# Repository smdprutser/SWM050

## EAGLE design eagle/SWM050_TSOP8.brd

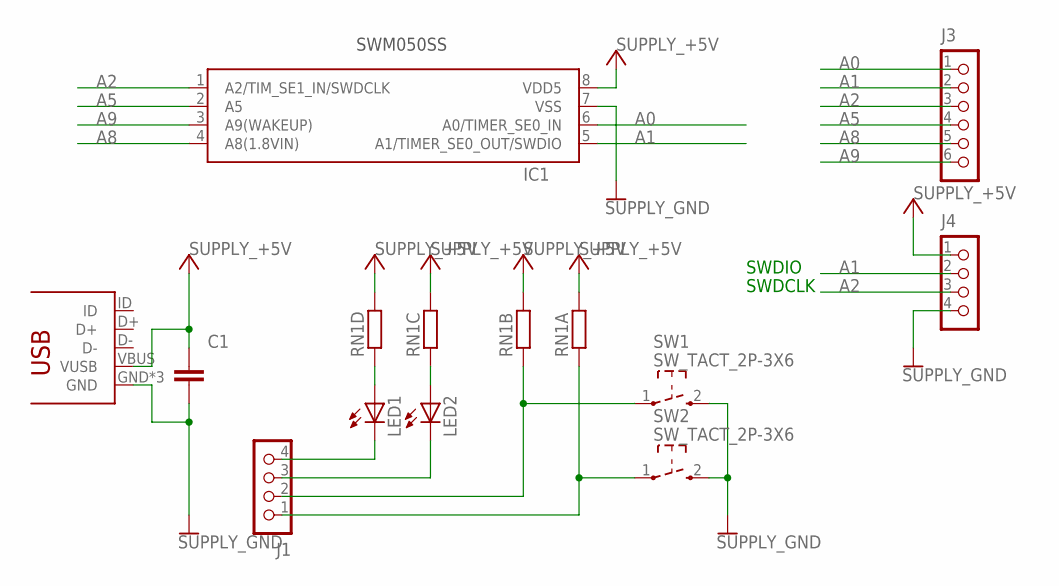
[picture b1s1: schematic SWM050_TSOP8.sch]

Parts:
C1: CAPACITOR_NPOL-0603; C603
IC1: SWM050I2P7""; TSOP8_065
J1, J4: CON_HEADER_1X04; M1X4
J3: CON_HEADER_1X06-PTH; M1X6
LED1, LED2: LED-0603; LED-603
RN1: RESISTOR_ARRAY_4; RN8P-4R-CRA06S
SW1, SW2: SW_TACT_2P-3X6; SW_TACT_3X6
U$1: CON_USB_MICRO_SMD; MICRO_USB_SMD

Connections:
+5V: C1.1, IC1.8 (VDD5), J4.1, RN1.5 (2), RN1.6 (2), RN1.7 (2), RN1.8 (2), U$1.VBUS (VUSB)
A0: IC1.6 (A0/TIMER_SE0_IN), J3.1
A1: IC1.5 (A1/TIMER_SE0_OUT/SWDIO), J3.2, J4.2
A2: IC1.1 (A2/TIM_SE1_IN/SWDCLK), J3.3, J4.3
A5: IC1.2 (A5), J3.4
A8: IC1.4 (A8(1.8VIN)), J3.5
A9: IC1.3 (A9(WAKEUP)), J3.6
GND: C1.2, IC1.7 (VSS), J4.4, SW1.2 (3), SW2.2 (3), U$1.GND, U$1.P$2 (GND), U$1.P$3 (GND)
unnamed: LED1.A, RN1.4 (1)
unnamed: LED2.A, RN1.3 (1)
unnamed: J1.2, RN1.2 (1), SW1.1
unnamed: J1.1, RN1.1, SW2.1
unnamed: J1.3, LED2.C
unnamed: J1.4, LED1.C

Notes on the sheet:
SWDIO
SWDCLK

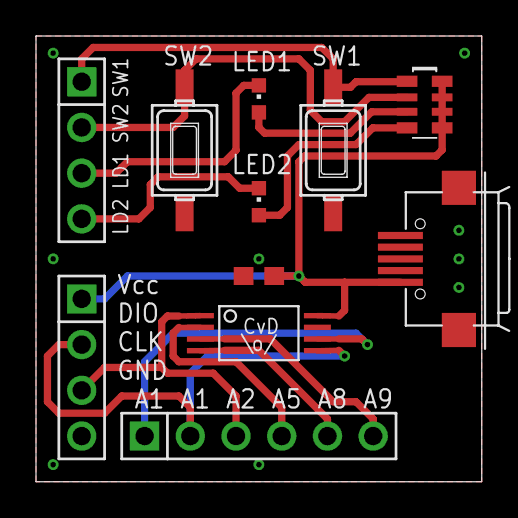
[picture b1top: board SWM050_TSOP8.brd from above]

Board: 2 copper layers, 24.8 x 24.8 mm, 12 parts (1 on the bottom side), 14 nets.

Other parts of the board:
U$2: SMDPRUTSER_LOGO_1INCH

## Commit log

2018-09-12 Initial import of library - 'machine translated' chinese comments in library to english - minimal crt0.s - Makefile - blinking led (A5) as example
2018-09-12 Add files via upload
    - Added eagle (v7) design files
    - Added Gerber files

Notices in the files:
eagle/SWM050_TSOP8.brd:
CC-BY-SA
